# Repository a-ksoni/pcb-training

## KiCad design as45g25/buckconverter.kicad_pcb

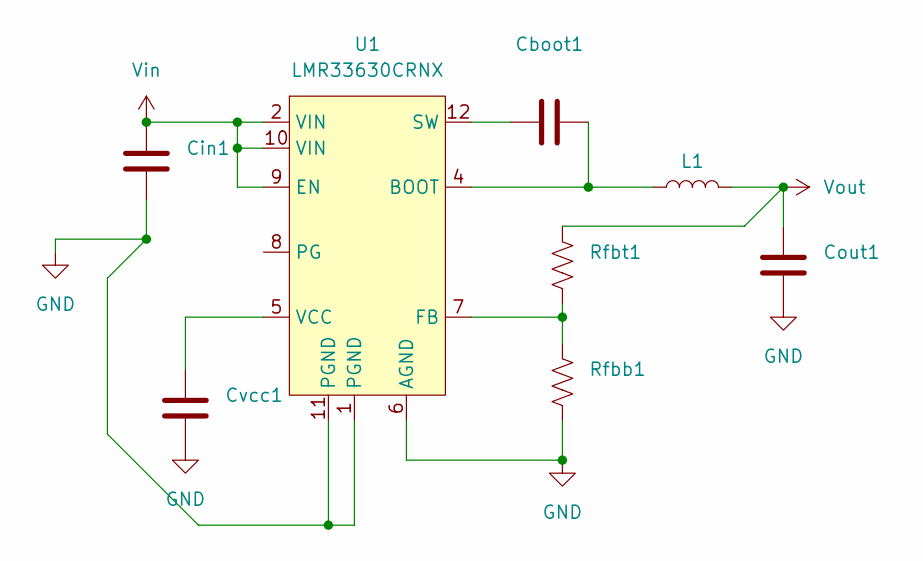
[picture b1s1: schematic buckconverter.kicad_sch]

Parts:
Cboot1: CP_Radial_D5.0mm_P2.50mm
Cin1: CP_Radial_D5.0mm_P2.50mm
Cout1: CP_Radial_D5.0mm_P2.50mm
Cvcc1: CP_Radial_D5.0mm_P2.50mm
L1: L_0805_2012Metric_Pad1.05x1.20mm_HandSolder
Rfbb1: R_1020_2550Metric_Pad1.33x5.20mm_HandSolder
Rfbt1: Rfbb; R_Axial_DIN0207_L6.3mm_D2.5mm_P5.08mm_Vertical
U1: LMR33630CRNX

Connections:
GND: Cin1.2, Cout1.2, Cvcc1.2, Rfbb1.2, U1.1 (PGND), U1.6 (AGND), U1.11 (PGND)
unnamed: Cboot1.2, L1.1, U1.4 (BOOT)
unnamed: Rfbb1.1, Rfbt1.2, U1.7 (FB)
unnamed: Cboot1.1, U1.12 (SW)
unnamed: Cvcc1.1, U1.5 (VCC)
Vin: Cin1.1, U1.2 (VIN), U1.9 (EN), U1.10 (VIN)
Vout: Cout1.1, L1.2, Rfbt1.1

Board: 2 copper layers, 8 parts (0 on the bottom side), 7 nets, no tracks yet.

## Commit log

2025-10-14 made a PCB buck converter
    made schem and pcb
